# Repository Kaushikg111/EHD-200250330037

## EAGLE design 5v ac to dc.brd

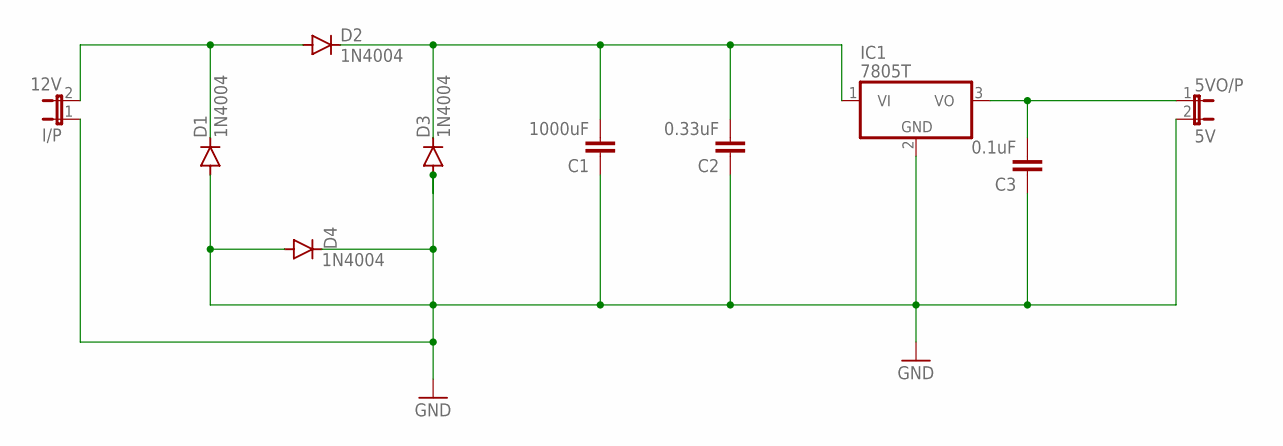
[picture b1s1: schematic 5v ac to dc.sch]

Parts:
5VO/P: 5V; JP1
C1: 1000uF; C2.5-3
C2: 0.33uF; C2.5-3
C3: 0.1uF; C2.5-3
D1, D2, D3, D4: 1N4004; DO41-10
I/P: 12V; JP1
IC1: 7805T; TO220H

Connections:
GND: 5VO/P.2, C1.1, C2.1, C3.1, D1.A, D3.A, D4.A, D4.C, I/P.1, IC1.2 (GND)
unnamed: D1.C, D2.A, I/P.2
unnamed: 5VO/P.1, C3.2, IC1.3 (VO)
unnamed: C1.2, C2.2, D2.C, D3.C, IC1.1 (VI)

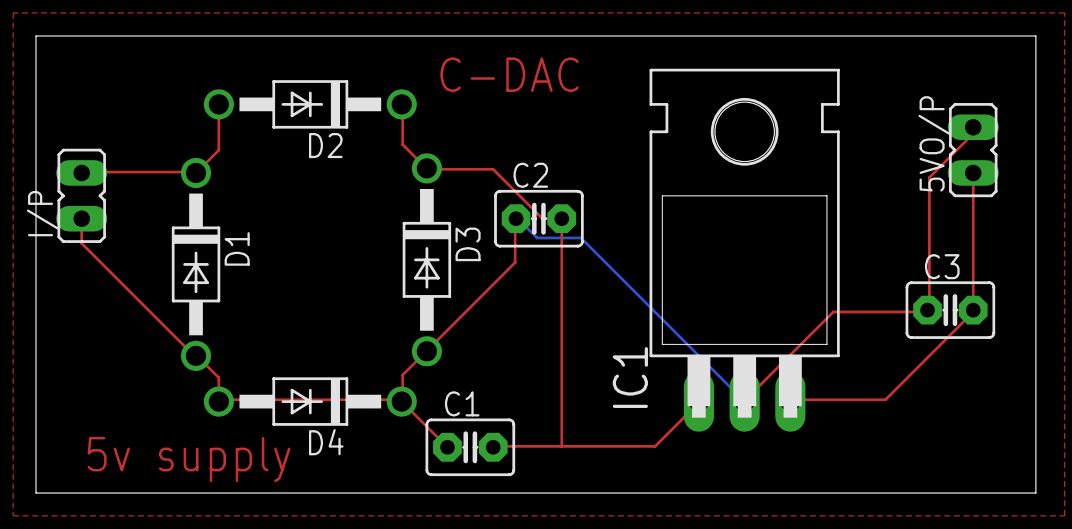
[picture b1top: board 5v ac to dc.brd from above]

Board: 2 copper layers, 55.6 x 25.4 mm, 10 parts (0 on the bottom side), 4 nets.

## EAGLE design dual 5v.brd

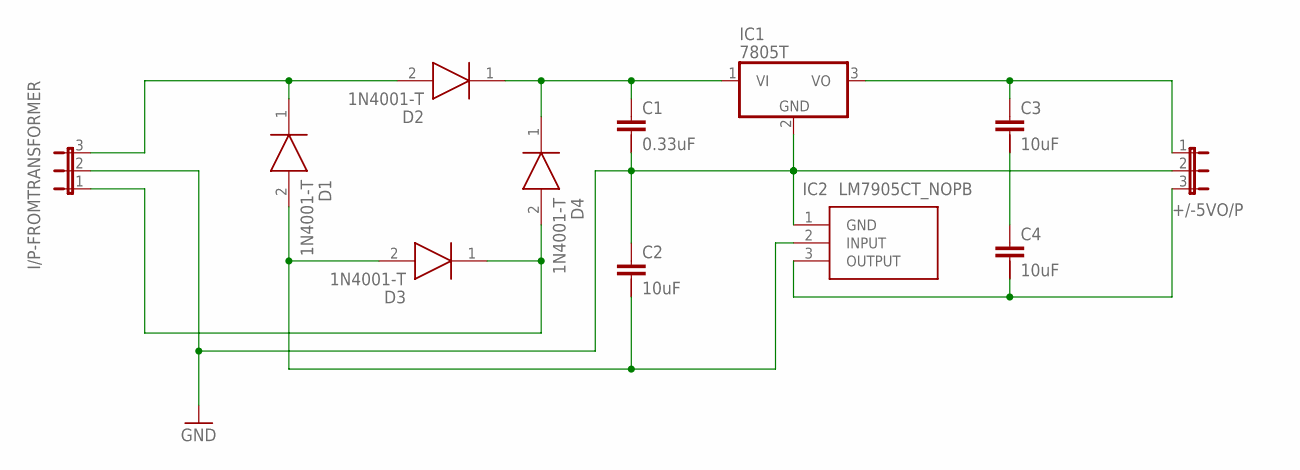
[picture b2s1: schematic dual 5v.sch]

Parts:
+/-5VO/P: JP2E; JP2
C1: 0.33uF; C2.5/5-2
C2, C3, C4: 10uF; C2.5/5-2
D1, D2, D3, D4: 1N4001-T; DIOAD1408W86L464D236
I/P-FROMTRANSFORMER: JP2E; JP2
IC1: 7805T; TO220H
IC2: LM7905CT_NOPB; TO254P470X1028X1955-3P

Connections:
GND: +/-5VO/P.2, C1.2, C2.1, I/P-FROMTRANSFORMER.2, IC1.2 (GND), IC2.1 (GND)
unnamed: D1.1 (K), D2.2 (A), I/P-FROMTRANSFORMER.3
unnamed: C1.1, D2.1 (K), D4.1 (K), IC1.1 (VI)
unnamed: C2.2, D1.2 (A), D3.2 (A), IC2.2 (INPUT)
unnamed: +/-5VO/P.3, C4.2, IC2.3 (OUTPUT)
unnamed: D3.1 (K), D4.2 (A), I/P-FROMTRANSFORMER.1
unnamed: +/-5VO/P.1, C3.1, IC1.3 (VO)
unnamed: C3.2, C4.1

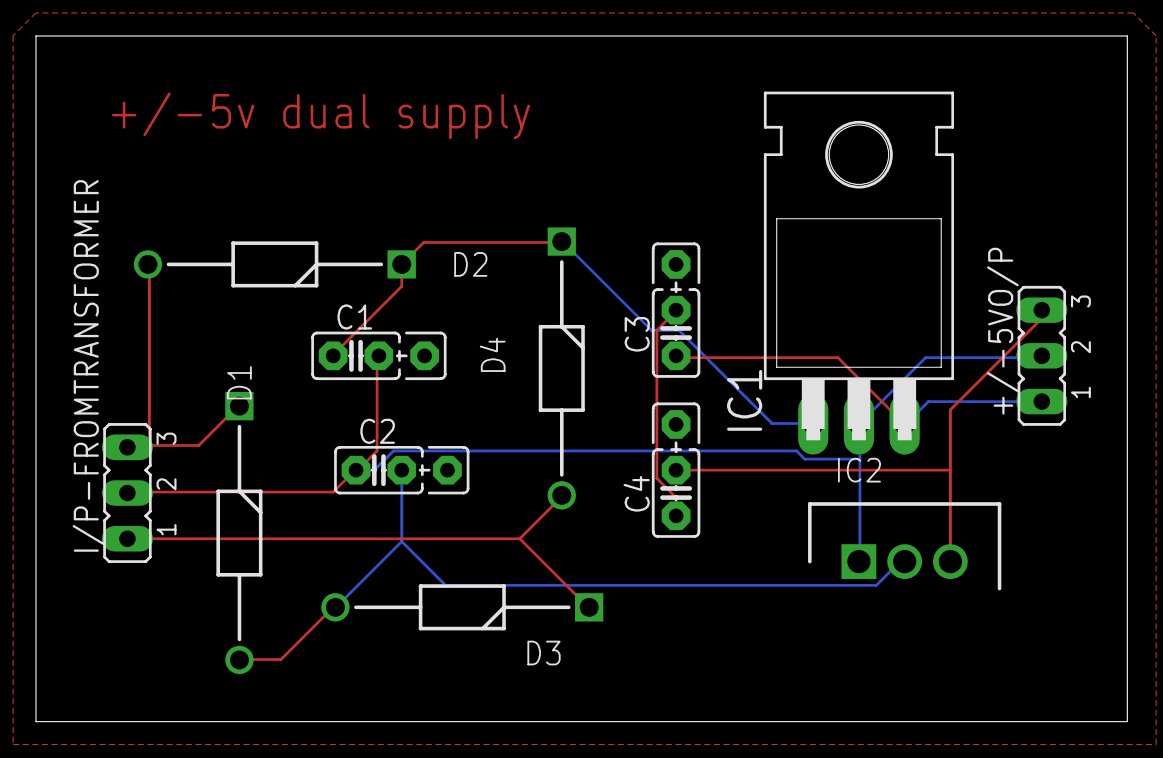
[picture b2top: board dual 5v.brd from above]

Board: 2 copper layers, 60.6 x 38.1 mm, 12 parts (0 on the bottom side), 8 nets.
